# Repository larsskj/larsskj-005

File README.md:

An LED tester for larsskj-003 boards
====================================

### larsskj-005

This board can be used to test LEDs connected to my larsskj-003 boards. It uses a NSI50010YT1G CCR (Constant Current Regulator) to source the LEDs with around 10 mA no matter the supply voltage.

SMD resistors may be used instead.

For more information, visit the [project homepage](https://larsskj.org/projects/larsskj-005).

The files provided are project files for [KiCad 5](http://kicad.org/).

The board is shared at [OSH Park](https://oshpark.com/shared_projects/7hGy0Jvt), where you can order copies.

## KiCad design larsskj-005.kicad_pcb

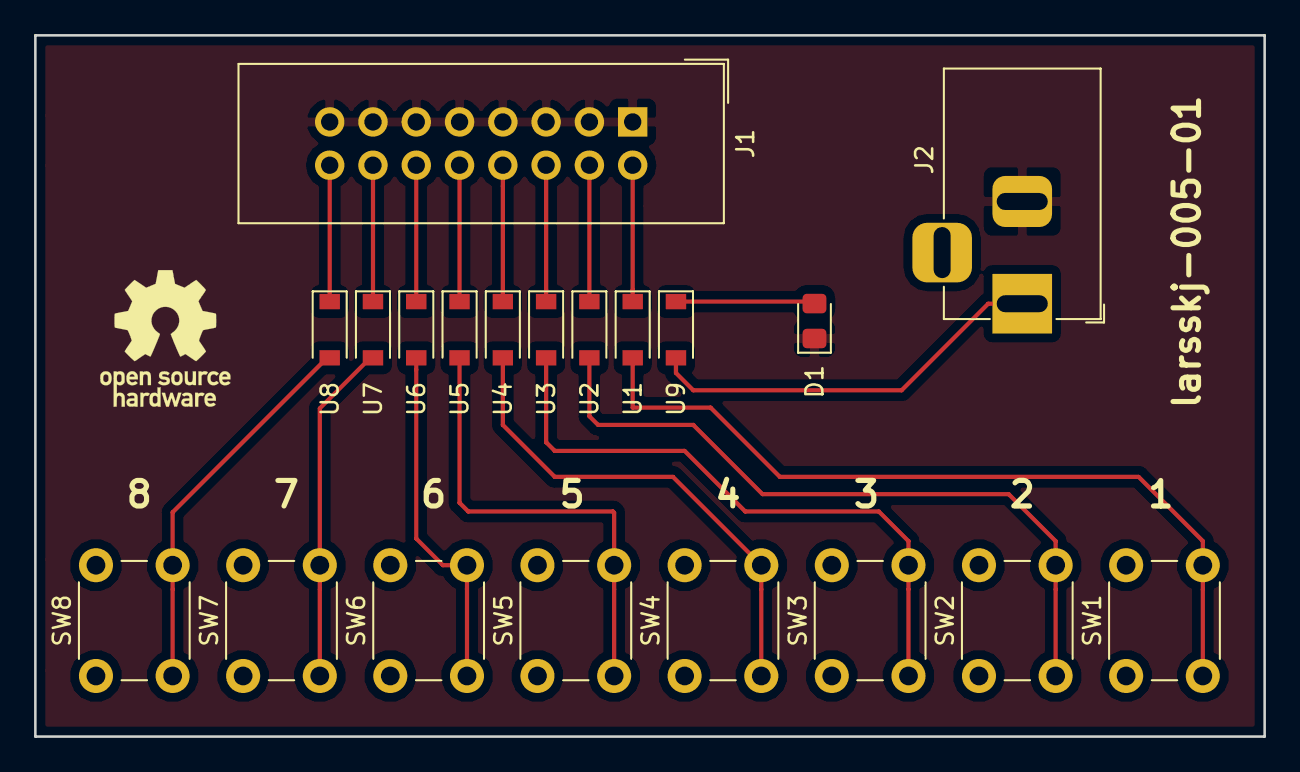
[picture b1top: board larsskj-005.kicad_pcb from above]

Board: 2 copper layers, 72.1 x 41.1 mm, 20 parts (0 on the bottom side), 19 nets.

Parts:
D1: LED; LED_0805_2012Metric_Pad1.15x1.40mm_HandSolder
J1: IDC 16 pin; IDC-Header_2x08_P2.54mm_Vertical
J2: Barrel_Jack; BarrelJack_Horizontal
SW1, SW2, SW3, SW4, SW5, SW6, SW7, SW8: SW_Push_SPDT; SW_PUSH_6mm_H5mm
U1, U2, U3, U4, U5, U6, U7, U9: NSI50010YT1G; D_SOD-123
U8: NSI50010YT1G x 8; D_SOD-123

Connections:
+VDC: J2.1, SW1.1, SW2.1, SW3.1, SW4.1, SW5.1, SW6.1, SW7.1, SW8.1, U9.2
GND: D1.1, J1.1, J1.3, J1.5, J1.7, J1.9, J1.11, J1.13, J1.15, J2.2
unnamed: D1.2, U9.1
unnamed: J1.2, U1.1
unnamed: J1.4, U2.1
unnamed: J1.6, U3.1
unnamed: J1.8, U4.1
unnamed: J1.10, U5.1
unnamed: J1.12, U6.1
unnamed: J1.14, U7.1
unnamed: J1.16, U8.1
unnamed: SW1.2, U1.2
unnamed: SW2.2, U2.2
unnamed: SW3.2, U3.2
unnamed: SW4.2, U4.2
unnamed: SW5.2, U5.2
unnamed: SW6.2, U6.2
unnamed: SW7.2, U7.2
unnamed: SW8.2, U8.2

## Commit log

2019-04-27 Initial import
2019-04-27 Documentation updates
2021-11-10 Update README.md
    https://forum.kicad.info/t/warning-avoid-all-links-to-kicad-pcb-org-use-kicad-org/31521
